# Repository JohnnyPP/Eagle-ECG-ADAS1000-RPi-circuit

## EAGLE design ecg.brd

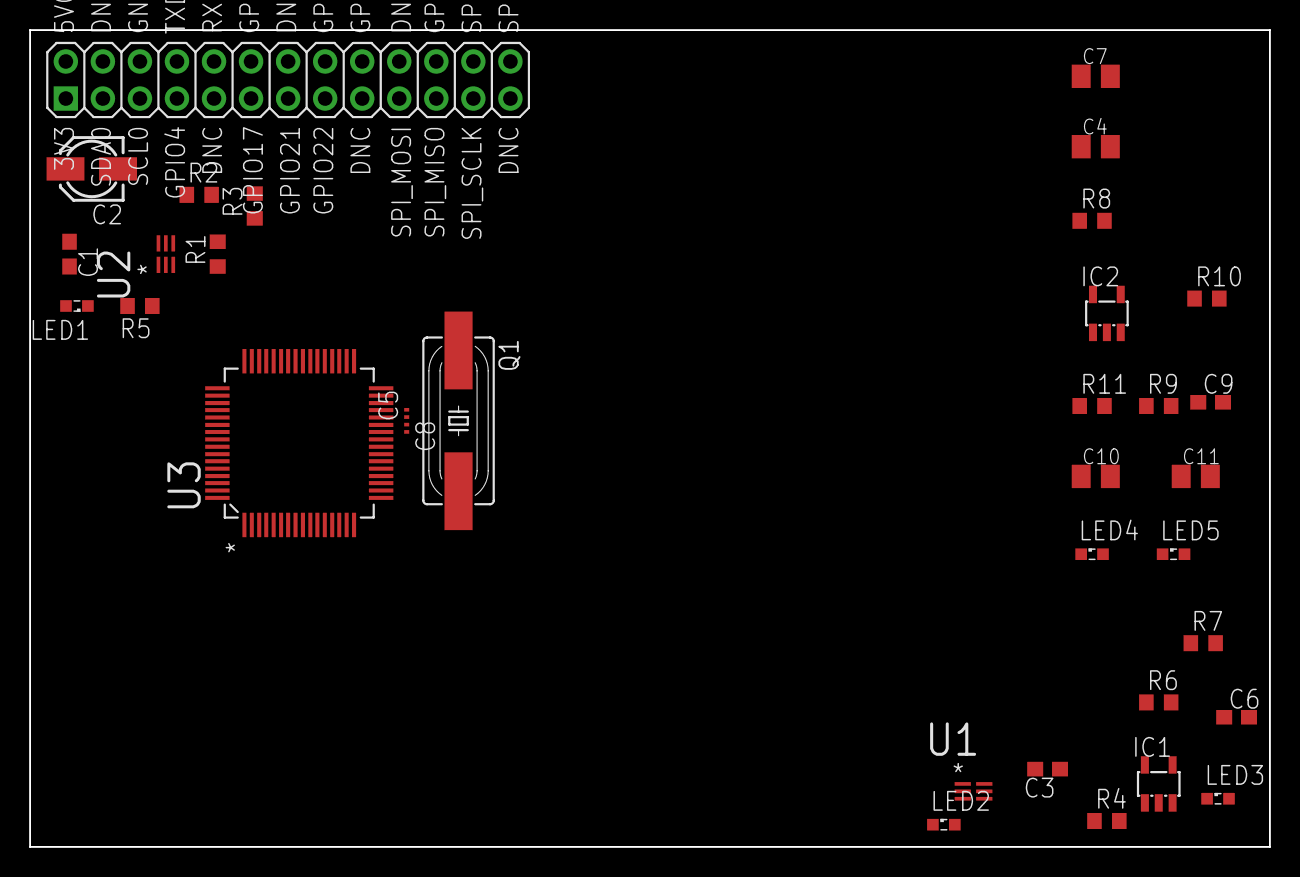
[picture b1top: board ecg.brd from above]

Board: 2 copper layers, 85.0 x 56.0 mm, 34 parts (0 on the bottom side), 18 nets, no tracks yet.

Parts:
C1, C3, C6, C9: 100n; C0603
C2: 10uF; 153CLV-0405
C4, C7, C10, C11: 10uF cer; C0805K
C5, C8: C0201
IC1, IC2: ADP151; SOT23-5
LED1, LED2, LED3, LED4, LED5: LED_SML0603
Q1: HC49UP
R1, R2, R3, R4, R5, R6, R7, R9, R10: 1k; R0603
R8, R11: 10k; R0603
RPI: RASPBERRYPI_BB; RASBERRYPI_SHIELD
U1, U2: TMP102AIDRLT; SOT50P160X60-6N
U3: ADAS1000BSTZ; QFP50P1200X1200X160-64N

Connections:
+3V3: C1.1, C2.+, C3.1, R1.2, R2.2, R3.2, R5.2, R6.2, RPI.1, U1.4, U1.5, U2.5
+3V3ADCVDD: C4.1, C6.1, IC1.5, R7.2
+3V3IOVDD: C9.1, C11.1, IC2.5, R10.2
+5V: C7.1, C10.1, IC1.1, IC2.1, R4.2, R8.2, R9.2, R11.2, RPI.2
GND: C1.2, C2.-, C3.2, C4.2, C5.2, C6.2, C7.2, C8.2, C9.2, C10.2, C11.2, IC1.2, IC2.2, LED1.C, LED2.C, LED3.C, LED4.C, LED5.C, RPI.6, U1.2, U2.2, U2.4
unnamed: R6.1, U1.3
unnamed: LED1.A, R5.1
unnamed: LED2.A, R4.1
unnamed: R1.1, U2.3
unnamed: LED3.A, R7.1
unnamed: C5.1, Q1.1, U3.28
unnamed: C8.1, Q1.2, U3.27
unnamed: IC1.3, R8.1
unnamed: LED4.A, R9.1
unnamed: LED5.A, R10.1
unnamed: IC2.3, R11.1
SCL: R3.1, RPI.5, U1.1, U2.1
SDA: R2.1, RPI.3, U1.6, U2.6

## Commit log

2014-03-13 Added TMP102 and ADAS1000 to schematics
2014-03-13 Replaced ADAS1000-2 (which is a slave device and cannot be used in standalone application) with ADAS1000BSTZ which is a master device
2014-03-16 Finished power supply on sch. Finished TMP102 circuits with I2C.
2014-03-22 Added XTAL
2014-03-22 Improved documentation
2014-03-23 Added second voltage regulator for digital domain. Changed the frame to a bigger one.
2014-03-29 The board is now horizontal
